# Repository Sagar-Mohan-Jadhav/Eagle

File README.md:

# Eagle
This repository is used to upload what I learn and whichever projects I do on Autodesk Eagle.

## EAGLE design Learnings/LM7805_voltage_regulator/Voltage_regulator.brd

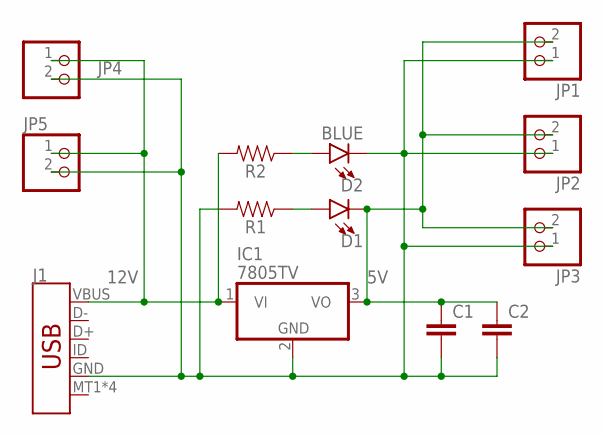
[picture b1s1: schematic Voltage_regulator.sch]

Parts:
C1, C2: C2,5-3; C2.5-3
D1: LED-GREEN0805-PG; LED-0805
D2: BLUE; LED-1206
IC1: 7805TV; TO220V
J1: USB_MICRO-B_SMT; USB-MICROB
JP1, JP2, JP3, JP4, JP5: PINHD-1X2; 1X02
R1, R2: 0805

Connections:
5V: C1.1, C2.1, D1.C, IC1.3 (VO), JP1.2, JP2.2, JP3.2
12V: IC1.1 (VI), J1.VBUS, JP4.1, JP5.1, R2.2
unnamed: C1.2, C2.2, D2.C, IC1.2 (GND), J1.GND, JP1.1, JP2.1, JP3.1, JP4.2, JP5.2, R1.2
unnamed: D2.A, R2.1
unnamed: D1.A, R1.1

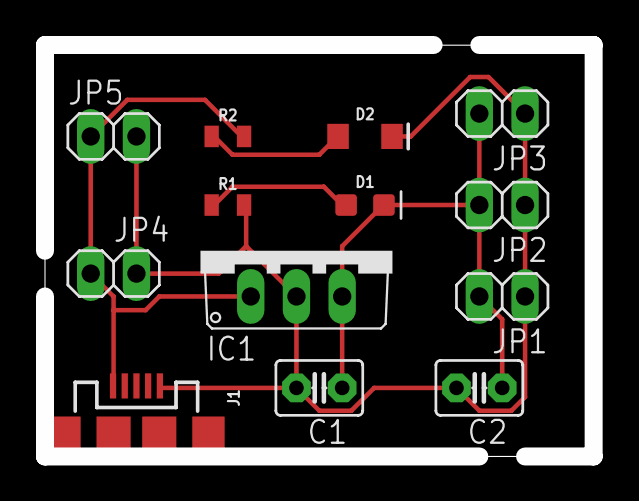
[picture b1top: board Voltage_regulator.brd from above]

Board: 2 copper layers, 30.5 x 22.9 mm, 13 parts (0 on the bottom side), 5 nets.

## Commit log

2023-03-07 LM7805_voltage_regulator
2023-03-07 completed circuit

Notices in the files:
parts and their libraries:
SparkFun-LED: Licensing: Creative Commons ShareAlike 4.0 International - https://creativecommons.org/licenses/by-sa/4.0
